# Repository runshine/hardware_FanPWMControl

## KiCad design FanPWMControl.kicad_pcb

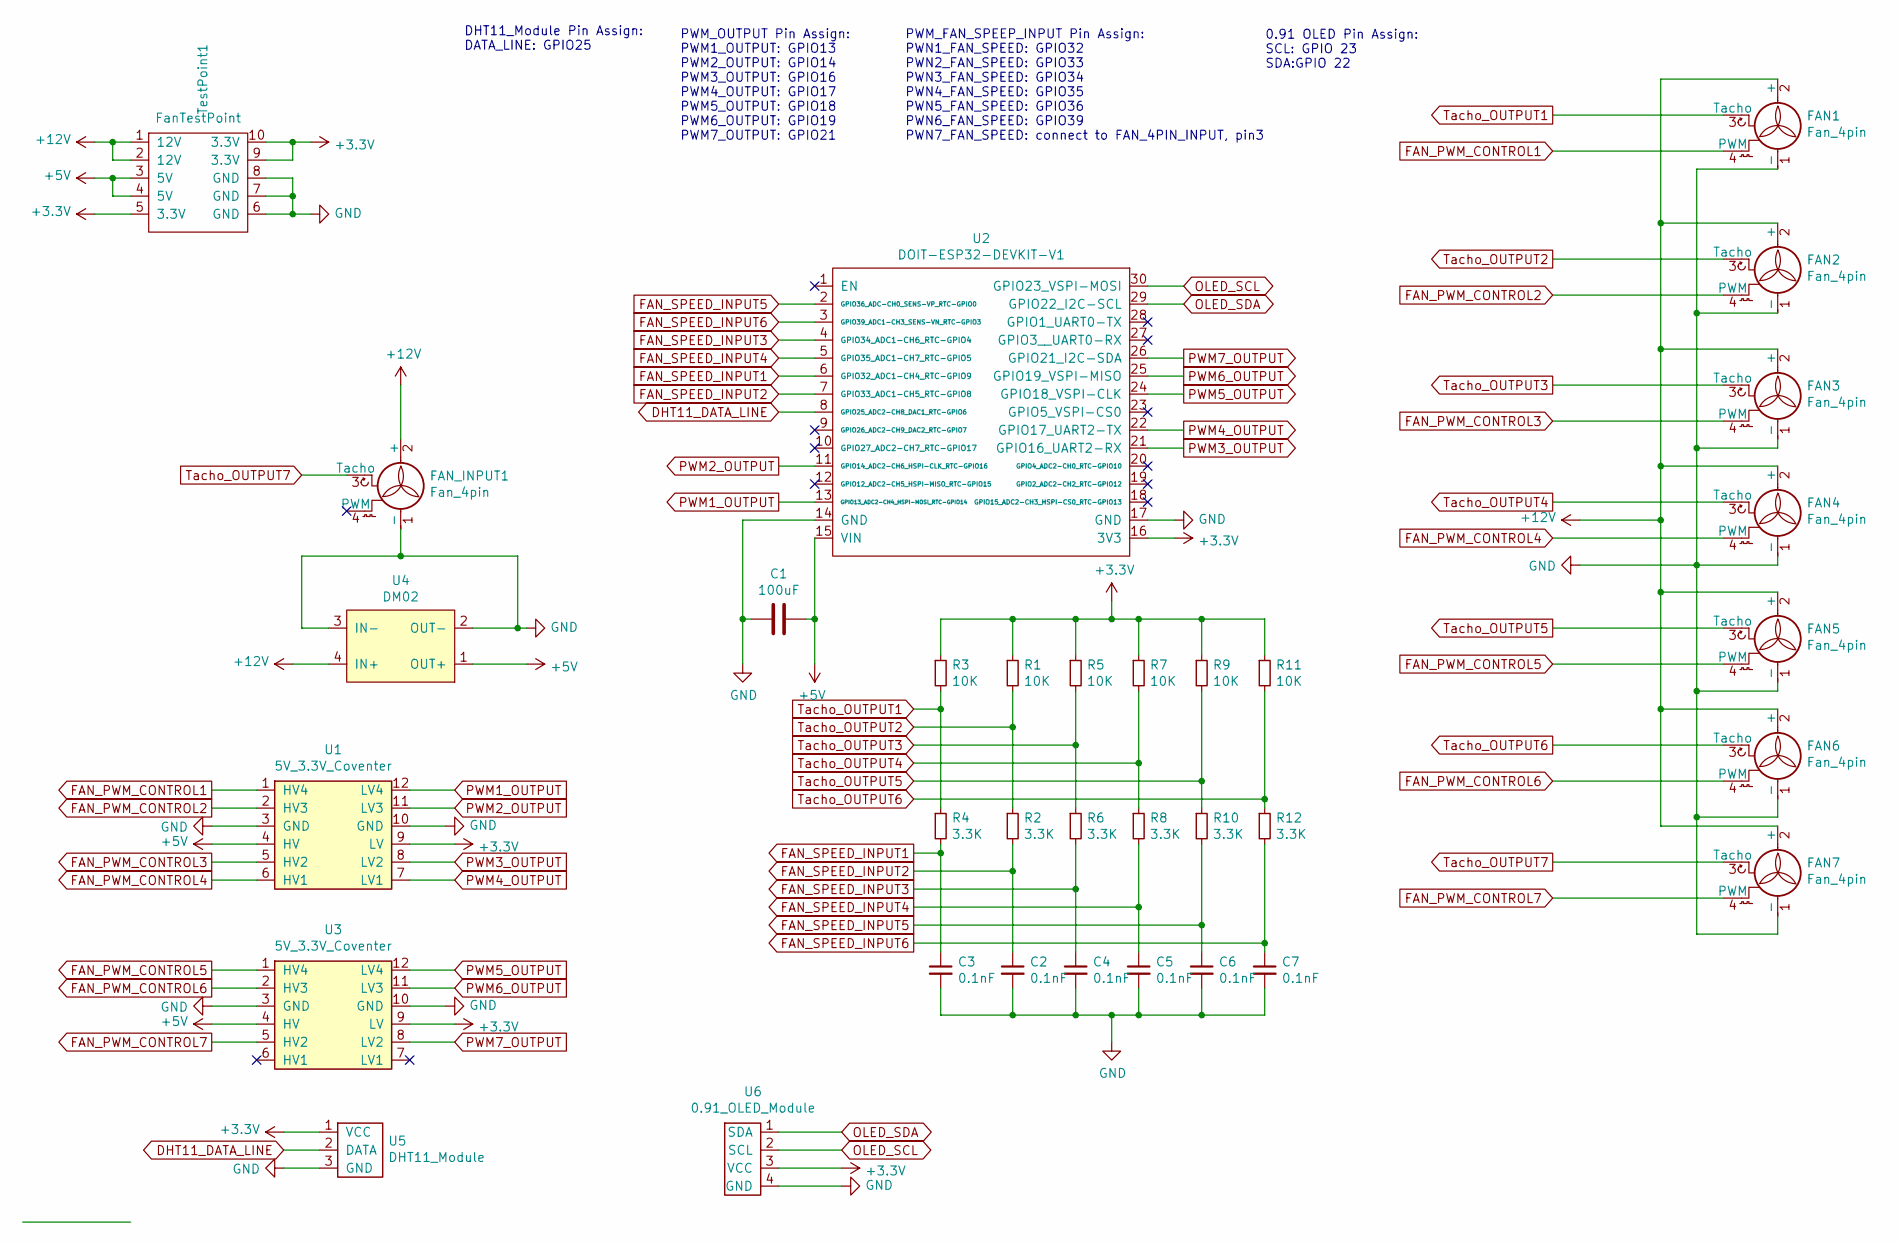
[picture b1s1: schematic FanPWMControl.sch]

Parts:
C1: 100uF; C_0805_2012Metric
C2, C3, C4, C5, C6, C7: 0.1nF; C_0805_2012Metric
FAN1, FAN2, FAN3, FAN4, FAN5, FAN6, FAN7: Fan_4pin; FanPinHeader_1x04_P2.54mm_Vertical
FAN_INPUT1: Fan_4pin; FanPinHeader_1x04_P2.54mm_Vertical
R1, R3, R5, R7, R9, R11: 10K; R_0805_2012Metric
R2, R4, R6, R8, R10, R12: 3.3K; R_0805_2012Metric
TestPoint1: FanTestPoint
U1, U3: 5V_3.3V_Coventer
U2: DOIT-ESP32-DEVKIT-V1; ESP32-DOIT-DEVKIT
U4: DM02
U5: DHT11_Module; DHT_Module
U6: 0.91_OLED_Module

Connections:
+3V3: R1.1, R3.1, R5.1, R7.1, R9.1, R11.1, TestPoint1.5 (3.3V), TestPoint1.9 (3.3V), TestPoint1.10 (3.3V), U1.9 (LV), U2.16 (3V3), U3.9 (LV), U5.1 (VCC), U6.3 (VCC)
+5V: C1.1, TestPoint1.3 (5V), TestPoint1.4 (5V), U1.4 (HV), U2.15 (VIN), U3.4 (HV), U4.1 (OUT+)
+12V: FAN1.2 (+), FAN2.2 (+), FAN3.2 (+), FAN4.2 (+), FAN5.2 (+), FAN6.2 (+), FAN7.2 (+), FAN_INPUT1.2 (+), TestPoint1.1 (12V), TestPoint1.2 (12V), U4.4 (IN+)
DHT11_DATA_LINE: U2.8 (GPIO25_ADC2-CH8_DAC1_RTC-GPIO6), U5.2 (DATA)
FAN_PWM_CONTROL1: FAN1.4 (PWM), U1.1 (HV4)
FAN_PWM_CONTROL2: FAN2.4 (PWM), U1.2 (HV3)
FAN_PWM_CONTROL3: FAN3.4 (PWM), U1.5 (HV2)
FAN_PWM_CONTROL4: FAN4.4 (PWM), U1.6 (HV1)
FAN_PWM_CONTROL5: FAN5.4 (PWM), U3.1 (HV4)
FAN_PWM_CONTROL6: FAN6.4 (PWM), U3.2 (HV3)
FAN_PWM_CONTROL7: FAN7.4 (PWM), U3.5 (HV2)
FAN_SPEED_INPUT1: C3.1, R4.2, U2.6 (GPIO32_ADC1-CH4_RTC-GPIO9)
FAN_SPEED_INPUT2: C2.1, R2.2, U2.7 (GPIO33_ADC1-CH5_RTC-GPIO8)
FAN_SPEED_INPUT3: C4.1, R6.2, U2.4 (GPIO34_ADC1-CH6_RTC-GPIO4)
FAN_SPEED_INPUT4: C5.1, R8.2, U2.5 (GPIO35_ADC1-CH7_RTC-GPIO5)
FAN_SPEED_INPUT5: C6.1, R10.2, U2.2 (GPIO36_ADC-CH0_SENS-VP_RTC-GPIO0)
FAN_SPEED_INPUT6: C7.1, R12.2, U2.3 (GPIO39_ADC1-CH3_SENS-VN_RTC-GPIO3)
GND: C1.2, C2.2, C3.2, C4.2, C5.2, C6.2, C7.2, FAN1.1 (-), FAN2.1 (-), FAN3.1 (-), FAN4.1 (-), FAN5.1 (-), FAN6.1 (-), FAN7.1 (-), FAN_INPUT1.1 (-), TestPoint1.6 (GND), TestPoint1.7 (GND), TestPoint1.8 (GND), U1.3 (GND), U1.10 (GND), U2.14 (GND), U2.17 (GND), U3.3 (GND), U3.10 (GND), U4.2 (OUT-), U4.3 (IN-), U5.3 (GND), U6.4 (GND)
OLED_SCL: U2.30 (GPIO23_VSPI-MOSI), U6.2 (SCL)
OLED_SDA: U2.29 (GPIO22_I2C-SCL), U6.1 (SDA)
PWM1_OUTPUT: U1.12 (LV4), U2.13 (GPIO13_ADC2-CH4_HSPI-MOSI_RTC-GPIO14)
PWM2_OUTPUT: U1.11 (LV3), U2.11 (GPIO14_ADC2-CH6_HSPI-CLK_RTC-GPIO16)
PWM3_OUTPUT: U1.8 (LV2), U2.21 (GPIO16_UART2-RX)
PWM4_OUTPUT: U1.7 (LV1), U2.22 (GPIO17_UART2-TX)
PWM5_OUTPUT: U2.24 (GPIO18_VSPI-CLK), U3.12 (LV4)
PWM6_OUTPUT: U2.25 (GPIO19_VSPI-MISO), U3.11 (LV3)
PWM7_OUTPUT: U2.26 (GPIO21_I2C-SDA), U3.8 (LV2)
Tacho_OUTPUT1: FAN1.3 (Tacho), R3.2, R4.1
Tacho_OUTPUT2: FAN2.3 (Tacho), R1.2, R2.1
Tacho_OUTPUT3: FAN3.3 (Tacho), R5.2, R6.1
Tacho_OUTPUT4: FAN4.3 (Tacho), R7.2, R8.1
Tacho_OUTPUT5: FAN5.3 (Tacho), R9.2, R10.1
Tacho_OUTPUT6: FAN6.3 (Tacho), R11.2, R12.1
Tacho_OUTPUT7: FAN7.3 (Tacho), FAN_INPUT1.3 (Tacho)

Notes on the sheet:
PWM_OUTPUT Pin Assign: PWM1_OUTPUT: GPIO13 PWM2_OUTPUT: GPIO14 PWM3_OUTPUT: GPIO16 PWM4_OUTPUT: GPIO17 PWM5_OUTPUT: GPIO18 PWM6_OUTPUT: GPIO19 PWM7_OUTPUT: GPIO21
PWM_FAN_SPEEP_INPUT Pin Assign: PWN1_FAN_SPEED: GPIO32 PWN2_FAN_SPEED: GPIO33 PWN3_FAN_SPEED: GPIO34 PWN4_FAN_SPEED: GPIO35 PWN5_FAN_SPEED: GPIO36 PWN6_FAN_SPEED: GPIO39 PWN7_FAN_SPEED: connect to FAN_4PIN_INPUT, pin3
DHT11_Module Pin Assign: DATA_LINE: GPIO25
0.91 OLED Pin Assign: SCL: GPIO 23 SDA:GPIO 22

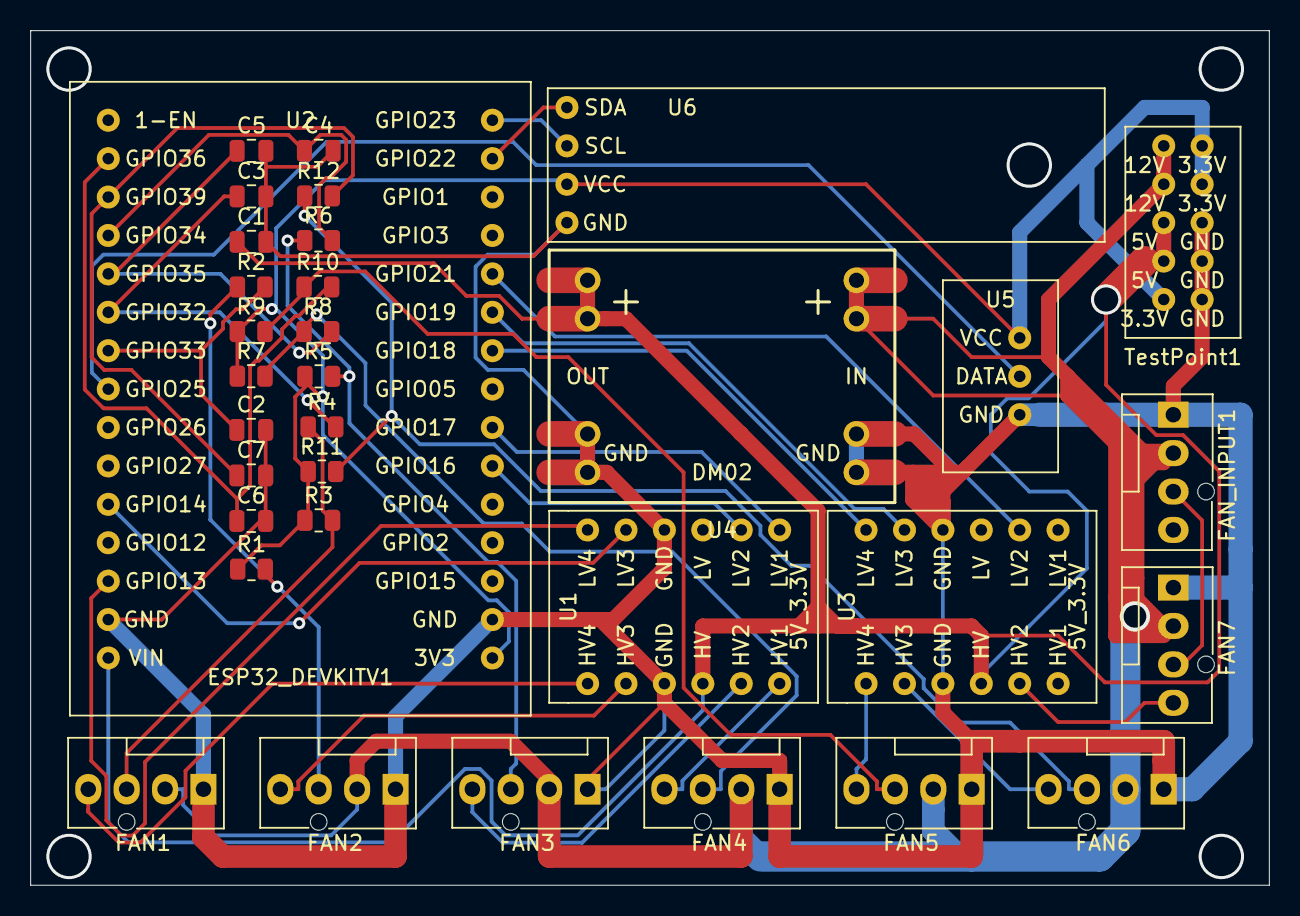
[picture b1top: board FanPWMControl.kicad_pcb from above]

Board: 2 copper layers, 81.9 x 56.5 mm, 34 parts (0 on the bottom side), 34 nets.
